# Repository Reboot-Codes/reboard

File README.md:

# ReBoard

A split ortholinear keyboard powered by QMK.

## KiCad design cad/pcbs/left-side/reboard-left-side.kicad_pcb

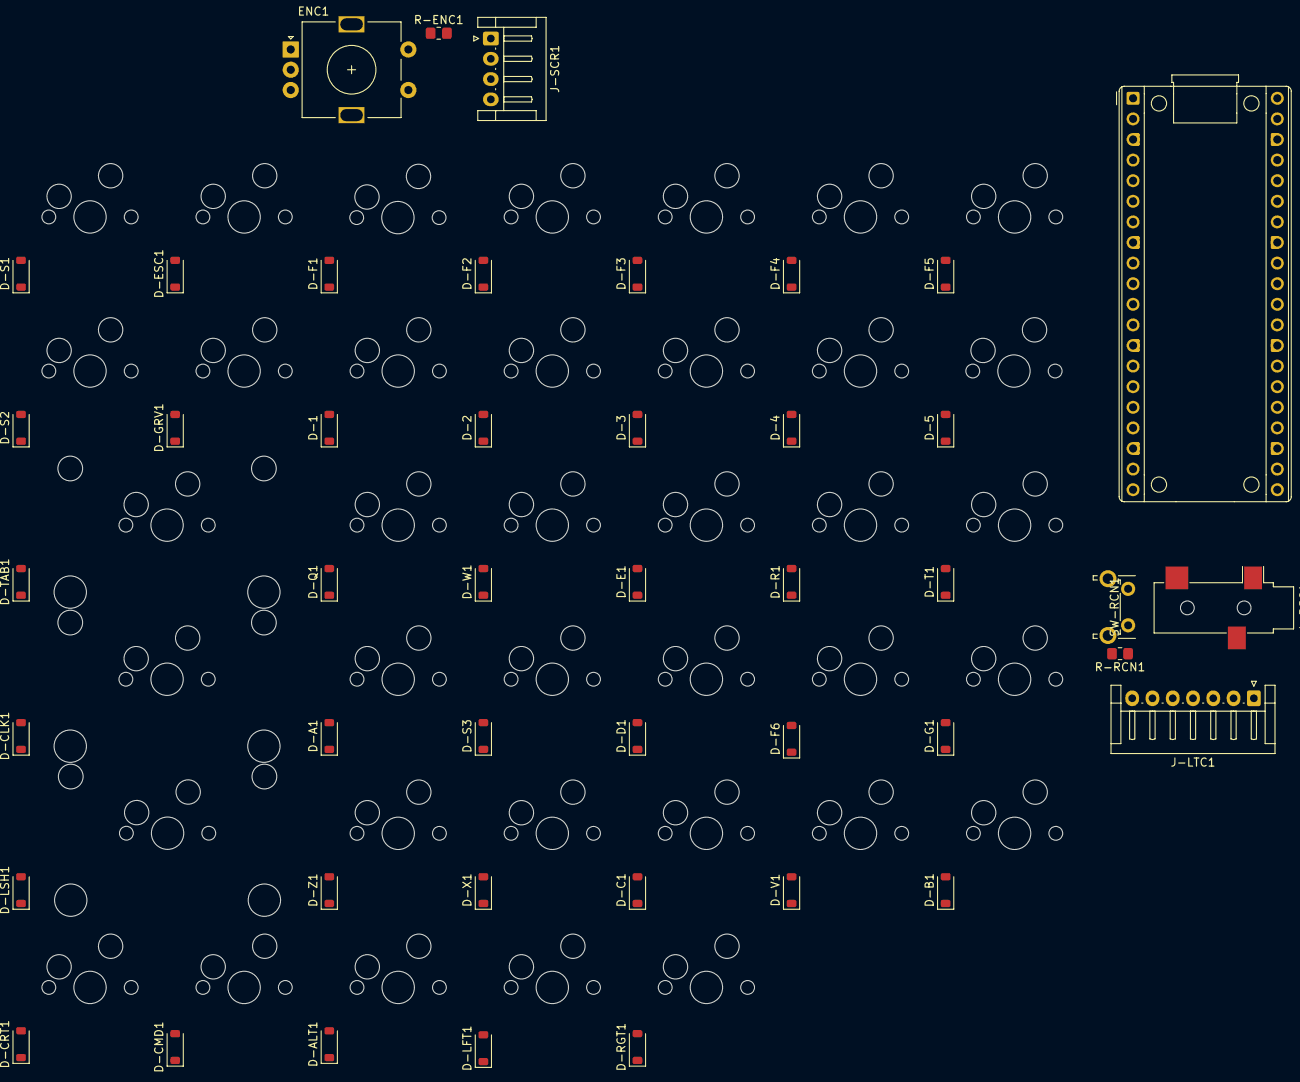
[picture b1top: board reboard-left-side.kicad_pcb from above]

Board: 2 copper layers, 82 parts (0 on the bottom side), 60 nets, no tracks yet.

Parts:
A1: RaspberryPi_Pico; RaspberryPi_Pico_Common_THT
D-1, D-2, D-3, D-4, D-5: D; D_SOD-123
D-A1: D; D_SOD-123
D-ALT1: D; D_SOD-123
D-B1: D; D_SOD-123
D-C1: D; D_SOD-123
D-CLK1: D; D_SOD-123
D-CMD1: D; D_SOD-123
D-CRT1: D; D_SOD-123
D-D1: D; D_SOD-123
D-E1: D; D_SOD-123
D-ESC1: D; D_SOD-123
D-F1, D-F2, D-F3, D-F4, D-F5, D-F6: D; D_SOD-123
D-G1: D; D_SOD-123
D-GRV1: D; D_SOD-123
D-LFT1: D; D_SOD-123
D-LSH1: D; D_SOD-123
D-Q1: D; D_SOD-123
D-R1: D; D_SOD-123
D-RGT1: D; D_SOD-123
D-S1, D-S2, D-S3: D; D_SOD-123
D-T1: D; D_SOD-123
D-TAB1: D; D_SOD-123
D-V1: D; D_SOD-123
D-W1: D; D_SOD-123
D-X1: D; D_SOD-123
D-Z1: D; D_SOD-123
ENC1: RotaryEncoder_Switch; RotaryEncoder_Alps_EC11E-Switch_Vertical_H20mm
J-LTC1: Conn_01x07_Socket; JST_EH_S7B-EH_1x07_P2.50mm_Horizontal
J-RSC1: AudioJack4; Jack_3.5mm_CUI_SJ-3523-SMT_Horizontal
J-SCR1: Conn_01x04; JST_EH_S4B-EH_1x04_P2.50mm_Horizontal
R-ENC1: R; R_0805_2012Metric_Pad1.20x1.40mm_HandSolder
R-RCN1: R; R_0805_2012Metric_Pad1.20x1.40mm_HandSolder
SW-1, SW-2, SW-3, SW-4, SW-5: SW_Push; MX-Hotswap-1U
SW-A1: SW_Push; MX-Hotswap-1U
SW-ALT1: SW_Push; MX-Hotswap-1U
SW-B1: SW_Push; MX-Hotswap-1U
SW-C1: SW_Push; MX-Hotswap-1U
SW-CLK1: SW_Push; MX-Hotswap-2U
SW-CMD1: SW_Push; MX-Hotswap-1U
SW-CRT1: SW_Push; MX-Hotswap-1U
SW-D1: SW_Push; MX-Hotswap-1U
SW-E1: SW_Push; MX-Hotswap-1U
SW-ESC1: SW_Push; MX-Hotswap-1U
SW-F1, SW-F2, SW-F3, SW-F4, SW-F5, SW-F6: SW_Push; MX-Hotswap-1U
SW-G1: SW_Push; MX-Hotswap-1U
SW-GRV1: SW_Push; MX-Hotswap-1U
SW-LFT1: SW_Push; MX-Hotswap-1U
SW-LSH1: SW_Push; MX-Hotswap-2U
SW-Q1: SW_Push; MX-Hotswap-1U
SW-R1: SW_Push; MX-Hotswap-1U
SW-RCN1: SW_Push; SW_Tactile_SPST_Angled_PTS645Vx31-2LFS
SW-RGT1: SW_Push; MX-Hotswap-1U
SW-S1, SW-S2, SW-S3: SW_Push; MX-Hotswap-1U
SW-T1: SW_Push; MX-Hotswap-1U
SW-TAB1: SW_Push; MX-Hotswap-2U
SW-V1: SW_Push; MX-Hotswap-1U
SW-W1: SW_Push; MX-Hotswap-1U
SW-X1: SW_Push; MX-Hotswap-1U
SW-Z1: SW_Push; MX-Hotswap-1U

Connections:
/COL-1: A1.12 (GPIO9), SW-CRT1.2, SW-S1.2, SW-S2.2
/COL-2: A1.14 (GPIO10), SW-CLK1.2, SW-CMD1.2, SW-ESC1.2, SW-GRV1.2, SW-LSH1.2, SW-TAB1.2
/COL-3: A1.15 (GPIO11), SW-1.2, SW-A1.2, SW-ALT1.2, SW-F1.2, SW-Q1.2, SW-Z1.2
/COL-4: A1.16 (GPIO12), SW-2.2, SW-F2.2, SW-LFT1.2, SW-S3.2, SW-W1.2, SW-X1.2
/COL-5: A1.17 (GPIO13), SW-3.2, SW-C1.2, SW-D1.2, SW-E1.2, SW-F3.2, SW-RGT1.2
/COL-6: A1.19 (GPIO14), J-LTC1.6, SW-4.2, SW-F4.2, SW-F6.2, SW-R1.2, SW-V1.2
/COL-7: A1.20 (GPIO15), J-LTC1.5, SW-5.2, SW-B1.2, SW-F5.2, SW-G1.2, SW-T1.2
/COL-8: A1.21 (GPIO16), J-LTC1.1
/ENC-A: A1.29 (GPIO22), ENC1.A
/ENC-B: A1.31 (GPIO26_ADC0), ENC1.B
/ENC-SW: A1.32 (GPIO27_ADC1), ENC1.S2, R-ENC1.1
/GND: A1.3 (GND), A1.8 (GND), A1.13 (GND), A1.18 (GND), A1.23 (GND), A1.28 (GND), A1.38 (GND), ENC1.C, J-SCR1.4, R-ENC1.2, R-RCN1.2
/RCN: A1.4 (GPIO2), R-RCN1.1, SW-RCN1.2
/ROW-1: A1.5 (GPIO3), D-ESC1.1 (K), D-F1.1 (K), D-F2.1 (K), D-F3.1 (K), D-F4.1 (K), D-F5.1 (K), D-S1.1 (K)
/ROW-2: A1.6 (GPIO4), D-1.1 (K), D-2.1 (K), D-3.1 (K), D-4.1 (K), D-5.1 (K), D-GRV1.1 (K), D-S2.1 (K)
/ROW-3: A1.7 (GPIO5), D-E1.1 (K), D-Q1.1 (K), D-R1.1 (K), D-T1.1 (K), D-TAB1.1 (K), D-W1.1 (K), J-LTC1.2
/ROW-4: A1.9 (GPIO6), D-A1.1 (K), D-CLK1.1 (K), D-D1.1 (K), D-F6.1 (K), D-G1.1 (K), D-S3.1 (K), J-LTC1.3
/ROW-5: A1.10 (GPIO7), D-B1.1 (K), D-C1.1 (K), D-LSH1.1 (K), D-V1.1 (K), D-X1.1 (K), D-Z1.1 (K), J-LTC1.4
/ROW-6: A1.11 (GPIO8), D-ALT1.1 (K), D-CMD1.1 (K), D-CRT1.1 (K), D-LFT1.1 (K), D-RGT1.1 (K), J-LTC1.7
/SCR-SCL: A1.27 (GPIO21), J-SCR1.2
/SCR-SDA: A1.26 (GPIO20), J-SCR1.1
/TRS: A1.1 (GPIO0), J-RSC1.T
/VCC: A1.36 (3V3), ENC1.S1, J-RSC1.S, J-SCR1.3, SW-RCN1.1
unnamed: D-1.2 (A), SW-1.1
unnamed: D-2.2 (A), SW-2.1
unnamed: D-3.2 (A), SW-3.1
unnamed: D-4.2 (A), SW-4.1
unnamed: D-5.2 (A), SW-5.1
unnamed: D-A1.2 (A), SW-A1.1
unnamed: D-ALT1.2 (A), SW-ALT1.1
unnamed: D-B1.2 (A), SW-B1.1
unnamed: D-C1.2 (A), SW-C1.1
unnamed: D-CLK1.2 (A), SW-CLK1.1
unnamed: D-CMD1.2 (A), SW-CMD1.1
unnamed: D-CRT1.2 (A), SW-CRT1.1
unnamed: D-D1.2 (A), SW-D1.1
unnamed: D-E1.2 (A), SW-E1.1
unnamed: D-ESC1.2 (A), SW-ESC1.1
unnamed: D-F1.2 (A), SW-F1.1
unnamed: D-F2.2 (A), SW-F2.1
unnamed: D-F3.2 (A), SW-F3.1
unnamed: D-F4.2 (A), SW-F4.1
unnamed: D-F5.2 (A), SW-F5.1
unnamed: D-F6.2 (A), SW-F6.1
unnamed: D-G1.2 (A), SW-G1.1
unnamed: D-GRV1.2 (A), SW-GRV1.1
unnamed: D-LFT1.2 (A), SW-LFT1.1
unnamed: D-LSH1.2 (A), SW-LSH1.1
unnamed: D-Q1.2 (A), SW-Q1.1
unnamed: D-R1.2 (A), SW-R1.1
unnamed: D-RGT1.2 (A), SW-RGT1.1
unnamed: D-S1.2 (A), SW-S1.1
unnamed: D-S2.2 (A), SW-S2.1
unnamed: D-S3.2 (A), SW-S3.1
unnamed: D-T1.2 (A), SW-T1.1
unnamed: D-TAB1.2 (A), SW-TAB1.1
unnamed: D-V1.2 (A), SW-V1.1
unnamed: D-W1.2 (A), SW-W1.1
unnamed: D-X1.2 (A), SW-X1.1
unnamed: D-Z1.2 (A), SW-Z1.1

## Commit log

2024-07-11 Finish Left Main-Board Layout
2024-07-11 Finish Left Main-Board Layout 2/2
